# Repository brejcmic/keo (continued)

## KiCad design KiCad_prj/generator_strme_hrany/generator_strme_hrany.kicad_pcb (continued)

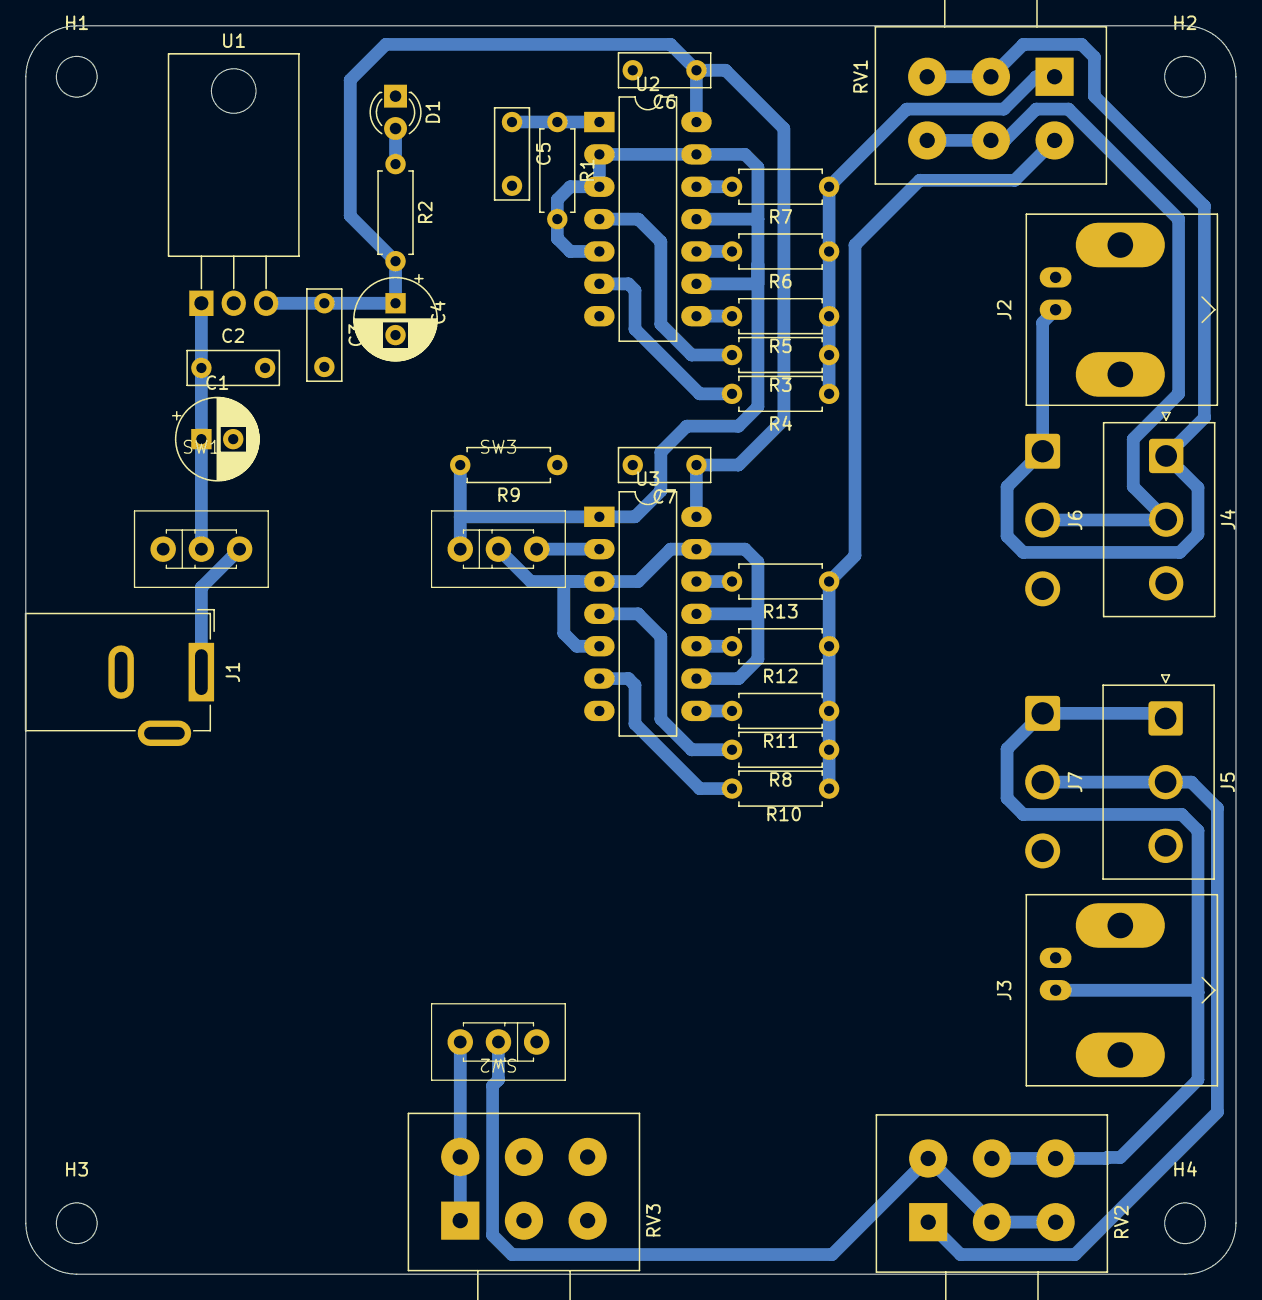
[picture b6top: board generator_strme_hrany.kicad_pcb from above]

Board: 2 copper layers, 95.0 x 98.0 mm, 41 parts (0 on the bottom side), 28 nets.

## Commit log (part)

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2021-09-20 Pocatecni verze prezentaci
2021-09-20 Oprava uvodni prezentace dle pozadavku 2021. Pridany ukazky praci studentu
2021-09-20 Změna ukazek praci studentu za tz, ktere lepe respektuji cile predmetu.
2021-10-05 Pripravena prezentace cviceni 3
2021-10-05 Upravena prezentace cviceni 2
2021-10-05 Uprava obrazku
2021-10-10 P4: novy projekt a knihovny
    Doplneny slajdy pro zalozeni noveho projektu a prirazeni vlastnich knihoven.
2021-10-18 P4: razitko a umistovani soucastek
2021-10-18 P4: temer dokoncene pridavani listu
2021-10-19 P4: dokončeny všechny body
2021-10-19 Pridan ukazkovy projekt
2021-10-19 Doplneni ukazkoveho projektu starym seznamem knihoven.
2022-09-19 Aktualizace roku
2023-10-02 Pridana prednaska 2 pro plosne spoje
2023-10-24 Predelani ukazkoveho projektu na verzi 7.0
2023-10-24 update prezentaci
2024-09-24 pridany obrazky instalace kicad 8.0.5
2024-09-29 Pridany simulace
2024-09-30 Uprava prezentace prototypu
2025-10-05 uprava cv3 2024
2025-10-05 Aktualizace prezentace cviceni cv3
2025-10-20 Simulace sinusoveho tvarovace signalu
2025-10-27 Simulace diferencialniho vedeni
2025-10-28 Navrh generatoru strme hrany
2025-10-30 Mosfet driver projekt
2025-11-02 Doplnen text do schematu a na dps
2025-11-02 Upravena adresarova struktura
2025-11-02 pridan zdroj do simulace crosstalk -> crosstalk_diff
2025-11-09 Mosfet driver v rev. 1.0 odeslan do vyroby
2025-11-10 pridana simulace dopredneho menice
2025-11-11 doplnen popis do simulace lt_spice_forward
2025-11-16 doplnena verze forward converter s kondenzatorem proti zemi
2025-11-19 Dokoncena DPS pripravku strme hrany
2025-11-21 Vyrobni data pro generator strme hrany
2025-11-25 Oprava budice na zaklade vysledku zkousek, pridano drazkovani
2025-11-26 Vytvořen symbol a pouzdro pro mosfet driver
2026-01-14 power_bank: navrh baterioveho obvodu
2026-01-15 power_bank: dokonceny navrh schema
2026-01-15 power_bank: doplnena pouzdra
2026-01-15 pocatek dps
2026-01-16 power_bank: priprava pouzdra chladice
2026-01-16 power_bank: zakladni vzhled DPS
2026-01-17 power_bank: vyrobni rozmisteni prvku, doplnit uzivatelske popisky
2026-01-17 power_bank: dokoncena DPS
2026-01-17 Odeslano do vyroby, rev 1.0
2026-01-28 Doplnen interaktivni BOM
2026-01-29 Oprava objednavaciho kodu u power_bank
